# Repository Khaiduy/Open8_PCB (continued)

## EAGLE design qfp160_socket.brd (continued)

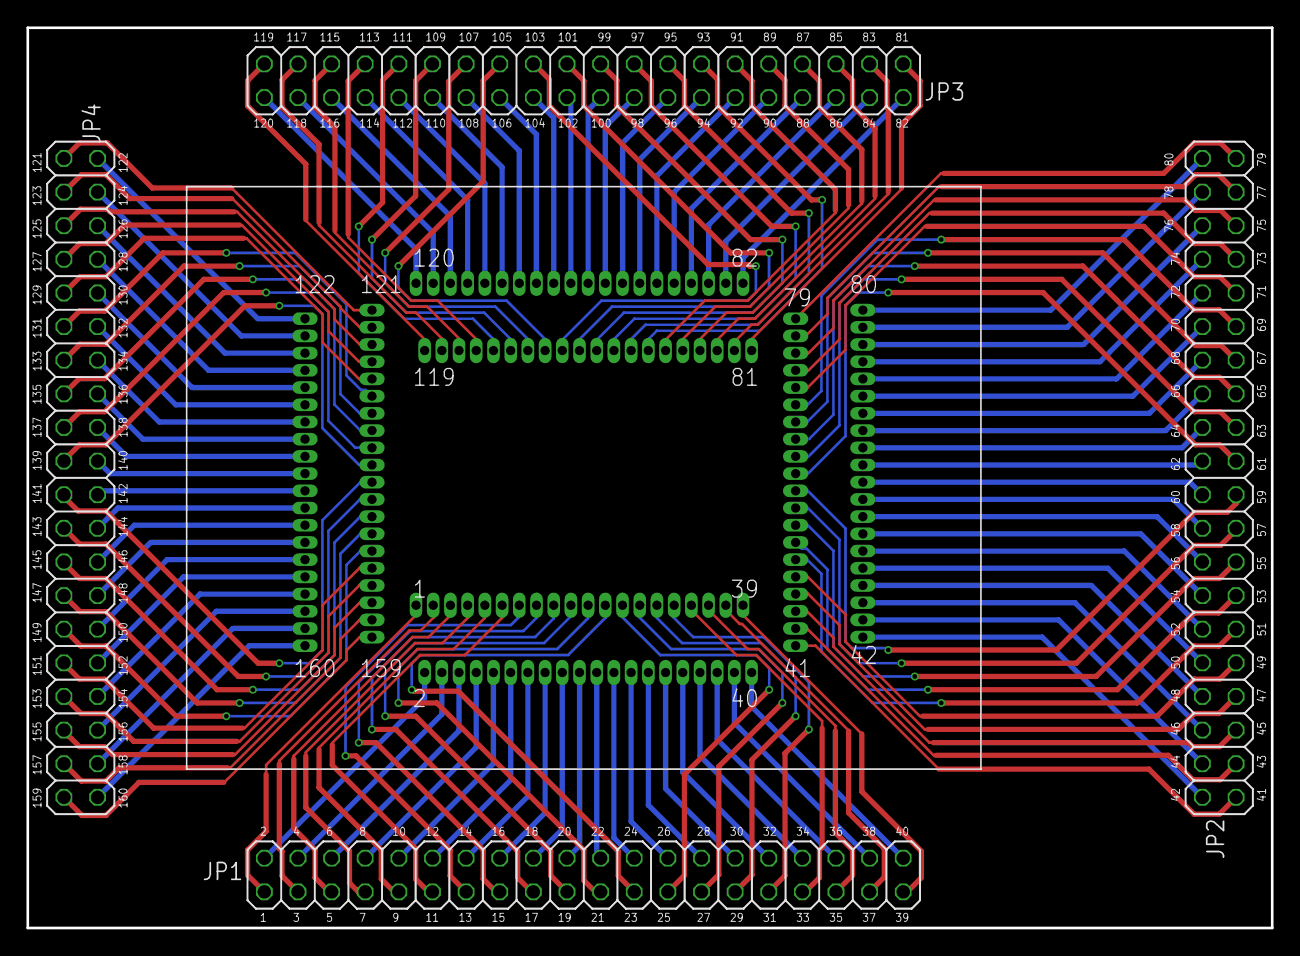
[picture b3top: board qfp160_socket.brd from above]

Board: 2 copper layers, 94.0 x 68.0 mm, 5 parts (0 on the bottom side), 160 nets.
